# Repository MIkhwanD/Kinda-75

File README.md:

# Kinda-75
 1st mech kbd using logitech 240

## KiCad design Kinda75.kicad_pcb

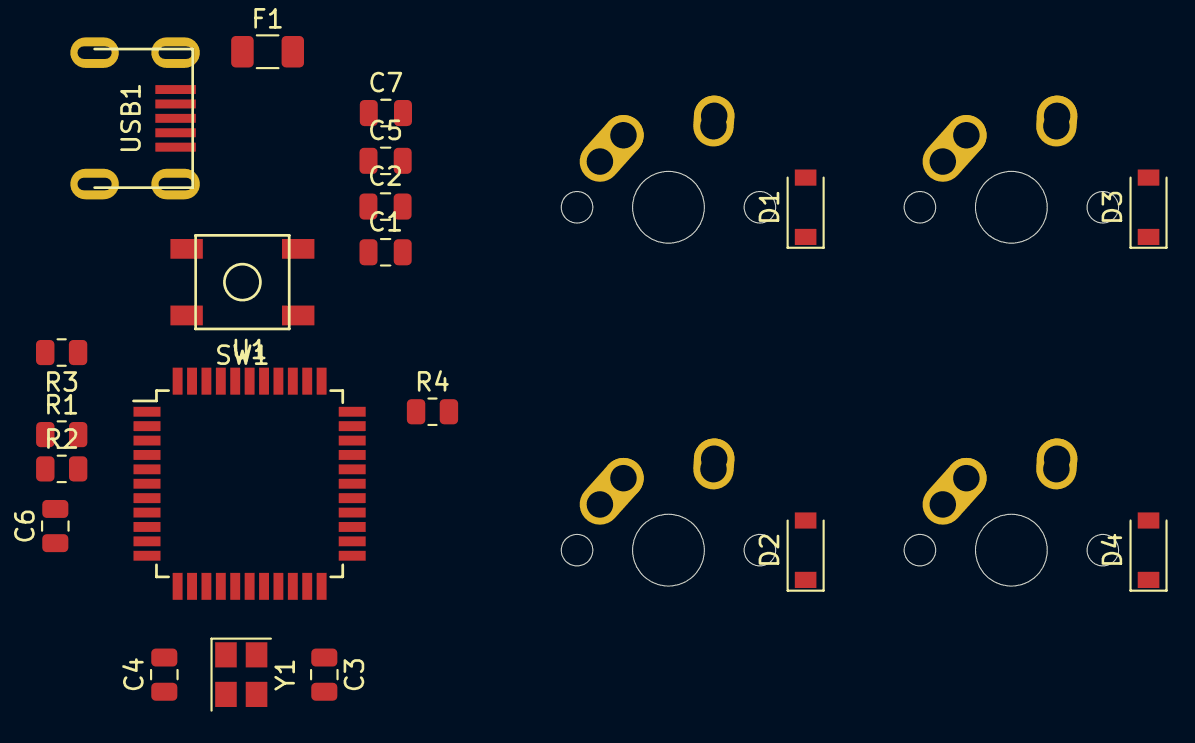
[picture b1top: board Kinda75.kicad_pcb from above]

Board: 2 copper layers, 24 parts (0 on the bottom side), 22 nets, no tracks yet.

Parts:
C1, C2, C5: 0.1uF; C_0805_2012Metric
C3, C4: 22pF; C_0805_2012Metric
C6: 1uF; C_0805_2012Metric
C7: 10uF; C_0805_2012Metric
D1, D2, D3, D4: SOD-123; D_SOD-123
F1: Polyfuse; Fuse_1206_3216Metric
MX1, MX2, MX3, MX4: MX-NoLED; MX-1U-NoLED
R1, R2: 22; R_0805_2012Metric
R3, R4: 10k; R_0805_2012Metric
SW1: SW_Push; SKQG-1155865
U1: ATmega32U4-A; TQFP-44_10x10mm_P0.8mm
USB1: Molex-0548190589
Y1: 16MHz; Crystal_SMD_3225-4Pin_3.2x2.5mm

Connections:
+5V: C1.1, C2.1, C5.1, C7.1, F1.2, R3.1, U1.2 (UVCC), U1.7 (VBUS), U1.14 (VCC), U1.34 (VCC)
/COL0: MX1.1 (COL), MX2.1 (COL)
/COL1: MX3.1 (COL), MX4.1 (COL)
/D+: R2.1, USB1.3 (D+)
/D-: R1.1, USB1.4 (D-)
/ROW0: D1.1 (K), D3.1 (K)
/ROW1: D2.1 (K), D4.1 (K)
GND: C1.2, C2.2, C3.1, C4.1, C5.2, C6.2, C7.2, R4.2, SW1.1, U1.5 (UGND), USB1.1 (GND), Y1.2, Y1.4
unnamed: C3.2, U1.17 (XTAL1), Y1.3
unnamed: C4.2, U1.16 (XTAL2), Y1.1
unnamed: C6.1, U1.6 (UCAP)
unnamed: D1.2 (A), MX1.2 (ROW)
unnamed: D2.2 (A), MX2.2 (ROW)
unnamed: D3.2 (A), MX3.2 (ROW)
unnamed: D4.2 (A), MX4.2 (ROW)
unnamed: F1.1, USB1.6 (SHIELD)
unnamed: R1.2, U1.3 (D-)
unnamed: R2.2, U1.4 (D+)
unnamed: R3.2, SW1.2, U1.13 (~RESET)
unnamed: R4.1, U1.33 (~HWB/PE2)
unnamed: U1.15 (GND), U1.23 (GND), U1.35 (GND), U1.43 (GND)
unnamed: U1.24 (AVCC), U1.44 (AVCC)

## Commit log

2022-01-04 Add submodules
